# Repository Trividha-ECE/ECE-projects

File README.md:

# ECE Projects

This repository contains my electronics and PCB design projects.

## Project 1: LM386 Audio Amplifier

**Description:**  
Designed a mini audio amplifier using LM386 IC to amplify weak audio signals.

**Software Used:**  
EasyEDA

**Components Used:**
- LM386 IC
- Capacitors
- Resistor
- Audio Input Connector
- Speaker Output Connector

## Circuit Schematic

## PCB 3D View

## Files Included
- Schematic_LM386-AMP-MONO.png
- LM386-PCB-3D.png
- LM386-AMP-MONO Circuit diagram .pdf
- SCH_LM386-AMP-MONO_2026-03-15.json
- Gerber_LM386-AMP-MONO_PCB_LM386-AMP-MONO_2_2026-03-10.zip

---

## Project 2: LED Blinking using NE555

### Description:

Designed an LED blinking circuit using NE555 timer IC in astable mode.

### 🔷 Circuit Schematic  

### 🔷 PCB Layout (2D)  

### 🔷 PCB 3D View  

### Features:

* Adjustable blinking speed
* Simple and beginner-friendly design

---

## Project 3: 5V to 10V Boost Converter using MT3608

### Description:

Designed a DC-DC boost converter PCB to step up 5V input to ~10V output using MT3608 IC.

### Software Used:

* KiCad

### Components Used:

* MT3608 IC
* Inductor
* Diode
* Capacitors
* Resistors

### Features:

* Compact PCB design
* Proper switching layout
* Stable output using feedback resistors

### Output:

* Input: 5V
* Output: ~10V

### Images:

---

## PCB 3D View

---

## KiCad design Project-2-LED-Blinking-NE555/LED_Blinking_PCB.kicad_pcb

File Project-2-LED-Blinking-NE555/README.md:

# NE555 LED Blinking Project

This project demonstrates a simple **LED blinking circuit** using the **NE555 timer IC**.  
The repository includes schematic, PCB layout, 2D & 3D images, and Gerber files for PCB manufacturing.

## Components Used
- NE555 Timer IC
- LED
- Resistors & Capacitors
- PCB layout designed in **KiCad**

## Schematic

## PCB Layout

## 3D View

## Gerber Files
The folder `LED_Blinking_Gerber_Final.zip` contains all manufacturing-ready Gerber files.

## How it Works
The NE555 timer is configured in **astable mode**, causing the LED to blink at a specific frequency.  
You can modify the resistors and capacitor values to change the blinking rate.

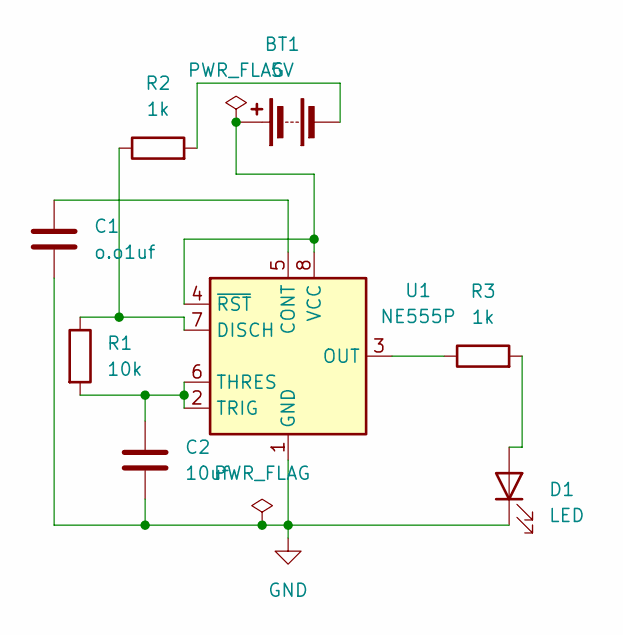
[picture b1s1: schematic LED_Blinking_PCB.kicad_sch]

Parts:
BT1: 5V; PinHeader_1x02_P2.54mm_Vertical
C1: o.o1uf; C_Disc_D5.0mm_W2.5mm_P2.50mm
C2: 10uf; CP_Radial_D5.0mm_P2.00mm
D1: LED; LED_D5.0mm
R1: 10k; R_Axial_DIN0207_L6.3mm_D2.5mm_P7.62mm_Horizontal
R2, R3: 1k; R_Axial_DIN0207_L6.3mm_D2.5mm_P7.62mm_Horizontal
U1: NE555P; DIP-8_W7.62mm

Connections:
GND: C1.2, C2.2, D1.1 (K), U1.1 (GND)
unnamed: BT1.1 (+), U1.4 (~RST), U1.8 (VCC)
unnamed: BT1.2 (-), R2.2
unnamed: D1.2 (A), R3.2
unnamed: C1.1, U1.5 (CONT)
unnamed: R1.1, R2.1, U1.7 (DISCH)
unnamed: R3.1, U1.3 (OUT)
unnamed: C2.1, R1.2, U1.2 (TRIG), U1.6 (THRES)

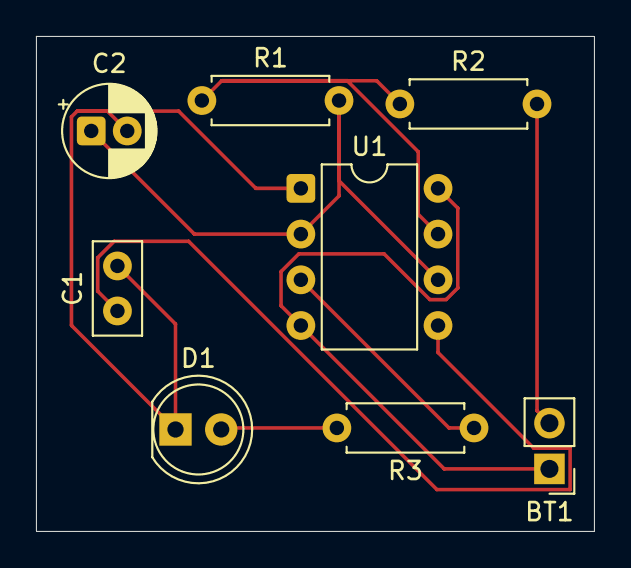
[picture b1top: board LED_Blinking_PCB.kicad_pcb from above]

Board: 2 copper layers, 31.0 x 27.5 mm, 8 parts (0 on the bottom side), 8 nets.

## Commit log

2026-03-15 Added LM386 audio amplifier schematic
    This project shows a mini audio amplifier circuit using LM386 IC designed in EasyEDA.
2026-03-15 Update README.md
    Added project details, components used, and description for LM386 audio amplifier schematic.
2026-03-15 Added LM386 amplifier circuit diagram PDF
    Uploaded PDF version of LM386 audio amplifier schematic designed in EasyEDA.
2026-03-15 Added EasyEDA source file for LM386 amplifier
    Uploaded EasyEDA JSON project file for LM386 mono audio amplifier schematic.
2026-03-15 Upload LM386 amplifier PCB Gerber files
    Gerber manufacturing files for LM386 mono audio amplifier PCB designed in EasyEDA.
2026-03-15 Added 3D PCB image for LM386 amplifier
    3D PCB layout image generated from EasyEDA for LM386 audio amplifier project.
2026-03-15 Update README.md
    Updated README to display schematic and 3D PCB images for LM386 amplifier project.
2026-04-07 Create README.md
    Added project description and details for LED blinking PCB using NE555 timer IC designed in KiCad.
2026-04-07 Added final Gerber files for NE555 LED blinking PCB
    Includes all manufacturing Gerber files generated from KiCad for LED blinking PCB using NE555 timer.
2026-04-07 Added KiCad schematic file for NE555 LED blinking PCB
    Schematic created using KiCad for LED blinking circuit using NE555 timer IC.
2026-04-07 LED_Blinking_PCB.kicad_pcb @Trividha-ECE Commit changes Commit summary Add files via upload Optional extended description Add an optional extended description… Commit directly to the main branch. Cre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
    KiCad PCB layout file containing component placement and routing for LED blinking circuit using NE555 timer.
2026-04-07 Added PCB 2D image for NE555 LED blinking project
    High-resolution 2D image of the NE555 LED blinking PCB layout generated from KiCad.
    Shows all component placements, tracks, and copper traces clearly for easy reference.
    This image complements the schematic and 3D PCB view in the repository.
2026-04-07 Added 3D PCB image for NE555 LED blinking project
    3D PCB view of the NE555 LED blinking circuit generated from KiCad.
    Shows component placement and spatial layout for a complete visual understanding of the PCB design.
2026-04-07 Added schematic image for NE555 LED blinking project
    High-resolution image of the NE555 LED blinking schematic showing all components and connections, exported from KiCad.
2026-04-07 Updated README with project description, schematic, PCB images, and details
2026-04-07 Create Project-3-Boost_Converter_MT3608_5V_to_10V
    This folder will contain all design files, images, and Gerber files for the Boost Converter project using MT3608 IC.
    The project steps up 5V input to 10V output and demonstrates a complete PCB design workflow using KiCad.
2026-04-08 Added Boost Converter schematic and project files
    Uploaded schematic design for 5V to 10V boost converter using MT3608 IC designed in KiCad.
2026-04-08 Added Boost Converter PCB (Gerber + KiCad + Images)
    Uploaded complete 5V to 10V boost converter design using MT3608 including PCB layout, schematic, and Gerber files.
2026-04-08 Added Boost Converter KiCad project files
    Uploaded KiCad project files for 5V to 10V boost converter using MT3608 including schematic and PCB design.
2026-04-08 Added PCB layout image for Boost Converter project
    Uploaded PCB layout screenshot showing component placement and routing for MT3608 boost converter.
2026-04-08 Added 3D view of Boost Converter PCB
    Uploaded 3D visualization of PCB showing component placement for MT3608 boost converter design.
2026-04-08 Update README.mdUpdated README with Project 2 (NE555) and Project 3 (Boost Converter) details and images
    Added detailed descriptions, features, and PCB images for LED blinking and boost converter projects to improve repository clarity and presentation.
